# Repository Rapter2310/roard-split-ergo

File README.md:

# Roard Keyboard

Roard is a custom wireless split keyboard I designed, heavily based on the Lily58. The main physical difference is the layout. I modified it to include a dedicated arrow key cluster on the right half. 

The biggest technical difference is the wireless setup. Instead of standard Bluetooth, I'm using a 3-node Nordic Enhanced ShockBurst (ESB) configuration. The left and right halves connect to a third nice!nano plugged into the PC acting as a dedicated dongle, which fixes the latency and connection drops you sometimes get with standard BLE splits.

## Hardware Details
* **Controllers:** 3x nice!nano v2 (left, right, and central dongle).
* **Displays:** 2x nice!view screens.
* **Switches & Sockets:** Gateron Aliaz (silent tactiles) seated in Kailh MX hotswap sockets.
* **Power:** 3.7v 110mAh LiPo batteries.
* **Components & Assembly:** Sourced all the board-level SMD components (diodes, power/reset switches, battery connectors, and sockets) directly from Typeractive, and assembled the board using Kester solder wire.
* **Design Tools:** The core layout was built in Keyboard Layout Editor (KLE). I initially used the ai03 plate generator for rapid prototyping to test different angles and ergonomics before committing to the board design. To map the final physical matrix to the firmware, I used the [ZMK Physical Layout Converter](https://zmk-physical-layout-converter.streamlit.app/) to translate the KLE JSON directly into ZMK layout macros. The raw design files are in the `/design` folder.
* **PCB:** Custom routed in KiCad. Once the routing and standoff placements were finalized, I exported the board as a STEP file to serve as the foundation for the mechanical design.

## Case & Mechanical
I modeled the enclosure from scratch in Onshape. To guarantee perfect switch alignment and mounting hole clearance, I imported the KiCad STEP file directly into my Onshape workspace and traced the final switch plates and case standoffs around the exact geometry of the PCB.

I used a few different materials for the 3D printed parts depending on what they needed to do:
* **Case & Switch Plate:** PETG for general strength.
* **Tenting Kit:** TPU so it actually grips the desk and dampens the sound a bit.
* **Display Covers:** PLA to protect the nice!view screens.
Everything is held together with standard brass standoffs.

## Current Status & WIP
The board is fully functional as my daily driver, but I'm currently working on two main things:

1. **Customizing the nice!view Screens:** Switching from standard BLE to the ESB dongle setup breaks the standard `nice!view` widget implementation, which relies on BLE Zephyr services to report full connection states. Currently, the screens are running a basic fallback ZMK display profile that only outputs battery levels. I am actively rewriting the display logic to pull layer information and connection states over the ESB protocol to restore full functionality.
2. **Custom Keycaps:** I'm in the process of generating and 3D printing a custom keycap profile using [PseudoMakeMeKeyCapProfiles](https://github.com/pseudoku/PseudoMakeMeKeyCapProfiles).

## Repository Structure
* `/design`: KLE json files and prototyping assets.
* `/docs`: Photos of the finished board, the PCB, and the tenting kit.
* `/firmware`: ZMK config files, custom shield definitions, and ESB dongle setup.
* `/hardware`: KiCad project files, schematics, and production-ready Gerbers.
* `/mechanical`: STLs for 3D printing and STEP files exported from Onshape.

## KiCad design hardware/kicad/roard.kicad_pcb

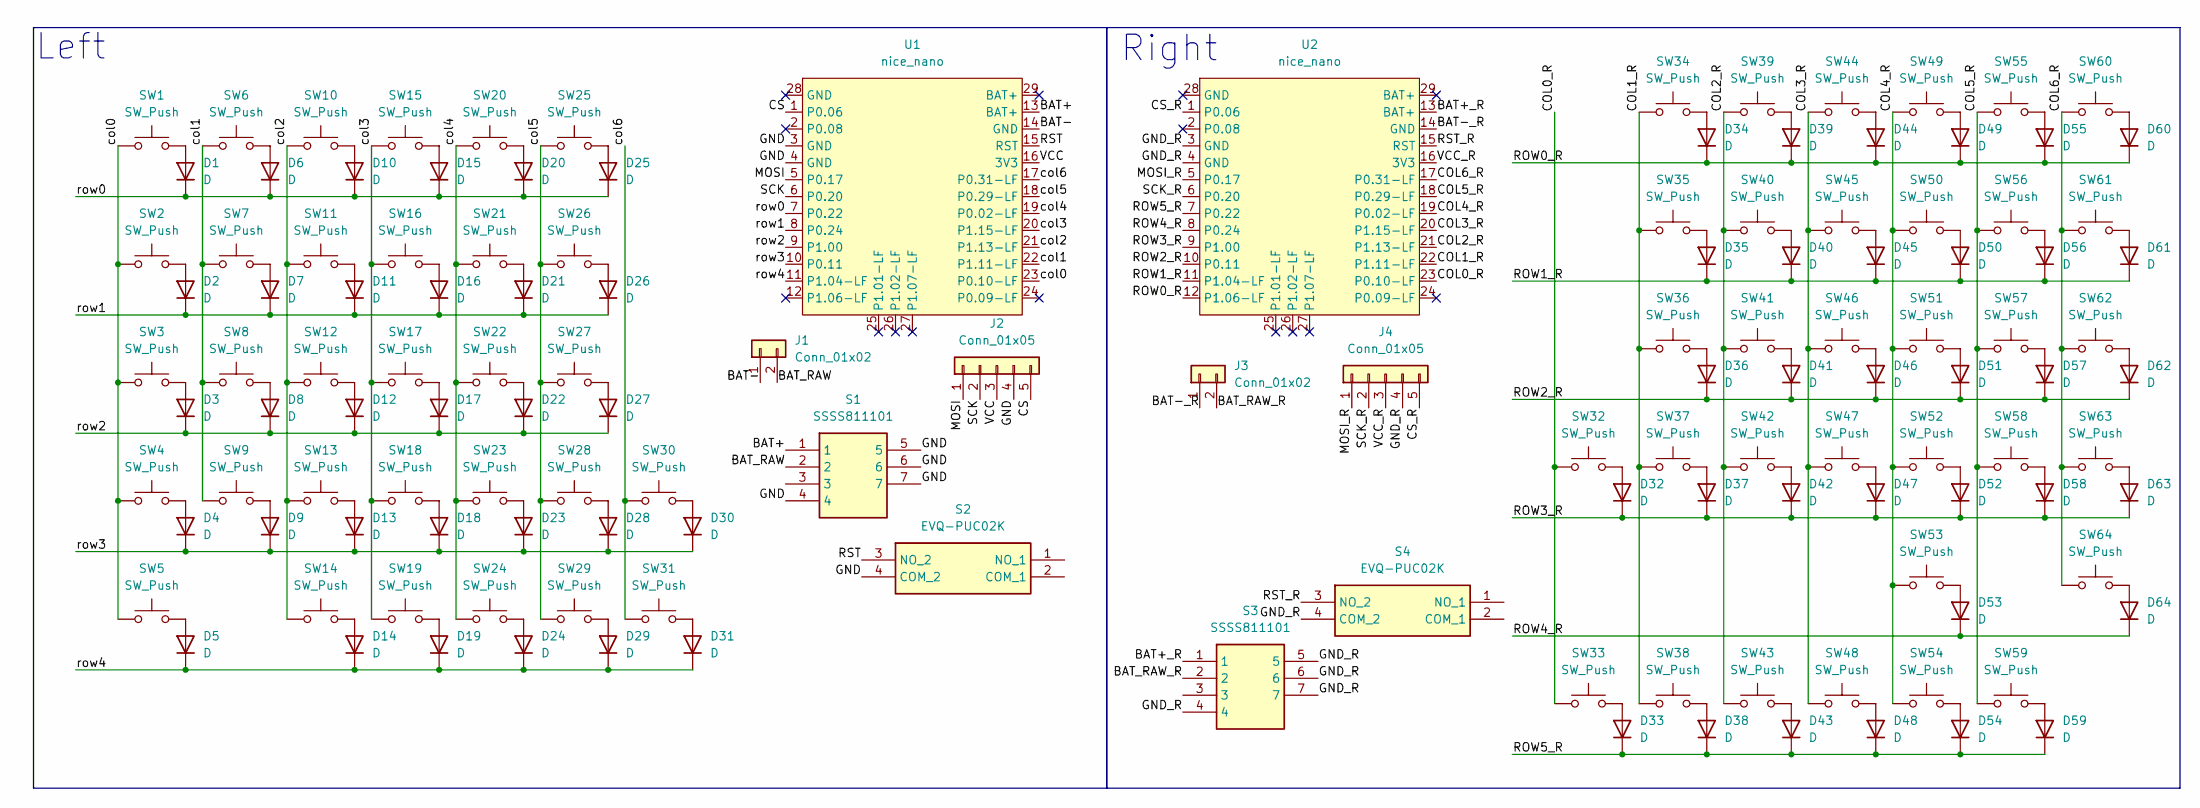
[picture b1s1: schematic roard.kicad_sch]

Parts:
D1, D2, D3, D4, D5, D6, D7, D8, D9, D10, D11, D12, D13, D14, D15, D16, D17, D18, D19, D20, D21, D22, D23, D24, D25, D26, D27, D28, D29, D30, D31, D32, D33, D34, D35, D36, D37, D38, D39, D40, D41, D42, D43, D44, D45, D46, D47, D48, D49, D50, D51, D52, D53, D54, D55, D56, D57, D58, D59, D60, D61, D62, D63, D64: D; D_SOD-123
J1, J3: Conn_01x02; JST_PH_S2B-PH-K_1x02_P2.00mm_Horizontal
J2, J4: Conn_01x05; PinHeader_1x05_P2.54mm_Vertical
S1, S3: SSSS811101; Mouser Part Number 688-SSSS811101
S2, S4: EVQ-PUC02K; EVQPUC02K; Mouser Part Number 667-EVQ-PUC02K
SW1, SW2, SW3, SW4, SW5, SW6, SW7, SW8, SW9, SW10, SW11, SW12, SW13, SW14, SW15, SW16, SW17, SW18, SW19, SW20, SW21, SW22, SW23, SW24, SW25, SW26, SW27, SW28, SW29, SW30, SW31, SW32, SW33, SW34, SW35, SW36, SW37, SW38, SW39, SW40, SW41, SW42, SW43, SW44, SW45, SW46, SW47, SW48, SW49, SW50, SW51, SW52, SW53, SW54, SW55, SW56, SW57, SW58, SW59, SW60, SW61, SW62, SW63, SW64: SW_Push; SW_Hotswap_Kailh_MX
U1, U2: nice_nano; nice_nano_pinChange

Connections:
/BAT+: S1.1, U1.13 (BAT+)
/BAT+_R: S3.1, U2.13 (BAT+)
/BAT-: J1.1, U1.14 (GND)
/BAT-_R: J3.1, U2.14 (GND)
/BAT_RAW: J1.2, S1.2
/BAT_RAW_R: J3.2, S3.2
/COL0_R: SW32.1, SW33.1, U2.23 (P0.10-LF)
/COL1_R: SW34.1, SW35.1, SW36.1, SW37.1, SW38.1, U2.22 (P1.11-LF)
/COL2_R: SW39.1, SW40.1, SW41.1, SW42.1, SW43.1, U2.21 (P1.13-LF)
/COL3_R: SW44.1, SW45.1, SW46.1, SW47.1, SW48.1, U2.20 (P1.15-LF)
/COL4_R: SW49.1, SW50.1, SW51.1, SW52.1, SW53.1, SW54.1, U2.19 (P0.02-LF)
/COL5_R: SW55.1, SW56.1, SW57.1, SW58.1, SW59.1, U2.18 (P0.29-LF)
/COL6_R: SW60.1, SW61.1, SW62.1, SW63.1, SW64.1, U2.17 (P0.31-LF)
/CS: J2.5, U1.1 (P0.06)
/CS_R: J4.5, U2.1 (P0.06)
/GND: J2.4, S1.4, S1.5, S1.6, S1.7, S2.4 (COM_2), U1.3 (GND), U1.4 (GND)
/GND_R: J4.4, S3.4, S3.5, S3.6, S3.7, S4.4 (COM_2), U2.3 (GND), U2.4 (GND)
/MOSI: J2.1, U1.5 (P0.17)
/MOSI_R: J4.1, U2.5 (P0.17)
/ROW0_R: D34.1 (K), D39.1 (K), D44.1 (K), D49.1 (K), D55.1 (K), D60.1 (K), U2.12 (P1.06-LF)
/ROW1_R: D35.1 (K), D40.1 (K), D45.1 (K), D50.1 (K), D56.1 (K), D61.1 (K), U2.11 (P1.04-LF)
/ROW2_R: D36.1 (K), D41.1 (K), D46.1 (K), D51.1 (K), D57.1 (K), D62.1 (K), U2.10 (P0.11)
/ROW3_R: D32.1 (K), D37.1 (K), D42.1 (K), D47.1 (K), D52.1 (K), D58.1 (K), D63.1 (K), U2.9 (P1.00)
/ROW4_R: D53.1 (K), D64.1 (K), U2.8 (P0.24)
/ROW5_R: D33.1 (K), D38.1 (K), D43.1 (K), D48.1 (K), D54.1 (K), D59.1 (K), U2.7 (P0.22)
/RST: S2.3 (NO_2), U1.15 (RST)
/RST_R: S4.3 (NO_2), U2.15 (RST)
/SCK: J2.2, U1.6 (P0.20)
/SCK_R: J4.2, U2.6 (P0.20)
/VCC: J2.3, U1.16 (3V3)
/VCC_R: J4.3, U2.16 (3V3)
/col0: SW1.1, SW2.1, SW3.1, SW4.1, SW5.1, U1.23 (P0.10-LF)
/col1: SW6.1, SW7.1, SW8.1, SW9.1, U1.22 (P1.11-LF)
/col2: SW10.1, SW11.1, SW12.1, SW13.1, SW14.1, U1.21 (P1.13-LF)
/col3: SW15.1, SW16.1, SW17.1, SW18.1, SW19.1, U1.20 (P1.15-LF)
/col4: SW20.1, SW21.1, SW22.1, SW23.1, SW24.1, U1.19 (P0.02-LF)
/col5: SW25.1, SW26.1, SW27.1, SW28.1, SW29.1, U1.18 (P0.29-LF)
/col6: SW30.1, SW31.1, U1.17 (P0.31-LF)
/row0: D1.1 (K), D6.1 (K), D10.1 (K), D15.1 (K), D20.1 (K), D25.1 (K), U1.7 (P0.22)
/row1: D2.1 (K), D7.1 (K), D11.1 (K), D16.1 (K), D21.1 (K), D26.1 (K), U1.8 (P0.24)
/row2: D3.1 (K), D8.1 (K), D12.1 (K), D17.1 (K), D22.1 (K), D27.1 (K), U1.9 (P1.00)
/row3: D4.1 (K), D9.1 (K), D13.1 (K), D18.1 (K), D23.1 (K), D28.1 (K), D30.1 (K), U1.10 (P0.11)
/row4: D5.1 (K), D14.1 (K), D19.1 (K), D24.1 (K), D29.1 (K), D31.1 (K), U1.11 (P1.04-LF)
unnamed: D1.2 (A), SW1.2
unnamed: D2.2 (A), SW2.2
unnamed: D3.2 (A), SW3.2
unnamed: D4.2 (A), SW4.2
unnamed: D5.2 (A), SW5.2
unnamed: D6.2 (A), SW6.2
unnamed: D7.2 (A), SW7.2
unnamed: D8.2 (A), SW8.2
unnamed: D9.2 (A), SW9.2
unnamed: D10.2 (A), SW10.2
unnamed: D11.2 (A), SW11.2
unnamed: D12.2 (A), SW12.2
unnamed: D13.2 (A), SW13.2
unnamed: D14.2 (A), SW14.2
unnamed: D15.2 (A), SW15.2
unnamed: D16.2 (A), SW16.2
unnamed: D17.2 (A), SW17.2
unnamed: D18.2 (A), SW18.2
unnamed: D19.2 (A), SW19.2
unnamed: D20.2 (A), SW20.2
unnamed: D21.2 (A), SW21.2
unnamed: D22.2 (A), SW22.2
unnamed: D23.2 (A), SW23.2
unnamed: D24.2 (A), SW24.2
unnamed: D25.2 (A), SW25.2
unnamed: D26.2 (A), SW26.2
unnamed: D27.2 (A), SW27.2
unnamed: D28.2 (A), SW28.2
unnamed: D29.2 (A), SW29.2
unnamed: D30.2 (A), SW30.2
unnamed: D31.2 (A), SW31.2
unnamed: D32.2 (A), SW32.2
unnamed: D33.2 (A), SW33.2
unnamed: D34.2 (A), SW34.2
unnamed: D35.2 (A), SW35.2
unnamed: D36.2 (A), SW36.2
unnamed: D37.2 (A), SW37.2
unnamed: D38.2 (A), SW38.2
unnamed: D39.2 (A), SW39.2
unnamed: D40.2 (A), SW40.2
unnamed: D41.2 (A), SW41.2
unnamed: D42.2 (A), SW42.2
unnamed: D43.2 (A), SW43.2
unnamed: D44.2 (A), SW44.2
unnamed: D45.2 (A), SW45.2
unnamed: D46.2 (A), SW46.2
unnamed: D47.2 (A), SW47.2
unnamed: D48.2 (A), SW48.2
unnamed: D49.2 (A), SW49.2
unnamed: D50.2 (A), SW50.2
unnamed: D51.2 (A), SW51.2
unnamed: D52.2 (A), SW52.2
unnamed: D53.2 (A), SW53.2
unnamed: D54.2 (A), SW54.2
unnamed: D55.2 (A), SW55.2
unnamed: D56.2 (A), SW56.2
unnamed: D57.2 (A), SW57.2
unnamed: D58.2 (A), SW58.2
unnamed: D59.2 (A), SW59.2
unnamed: D60.2 (A), SW60.2
unnamed: D61.2 (A), SW61.2
unnamed: D62.2 (A), SW62.2
unnamed: D63.2 (A), SW63.2
unnamed: D64.2 (A), SW64.2

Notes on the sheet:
Right
Left

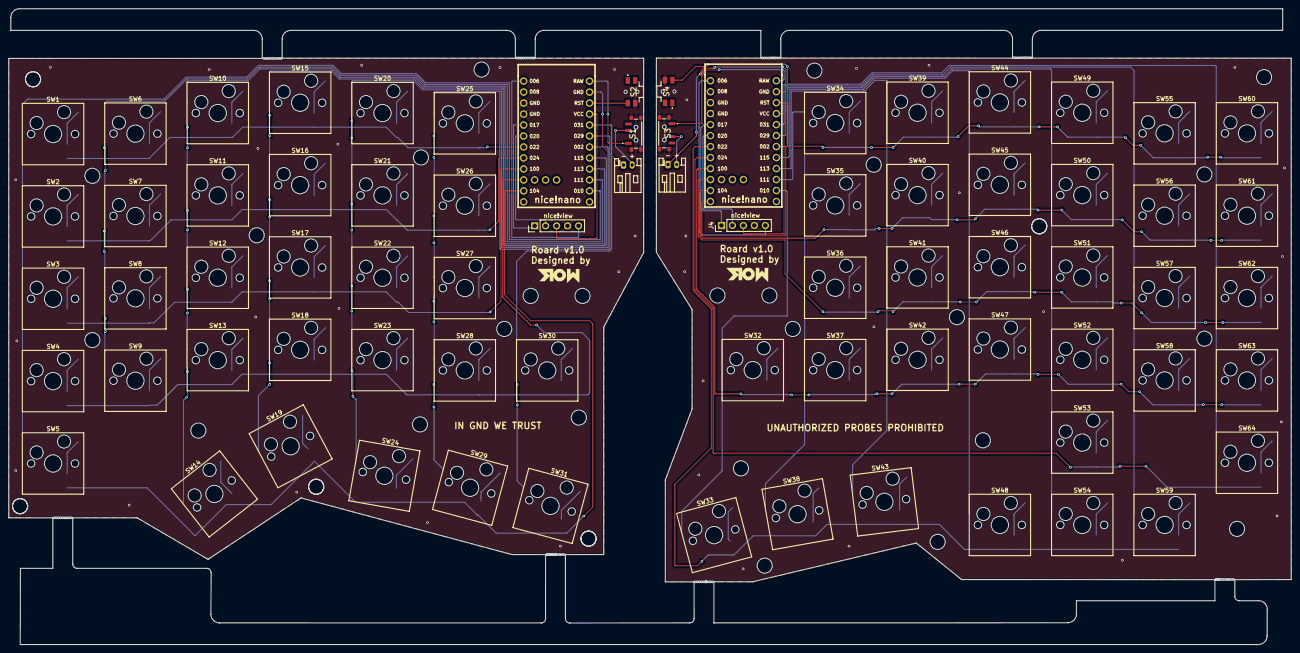
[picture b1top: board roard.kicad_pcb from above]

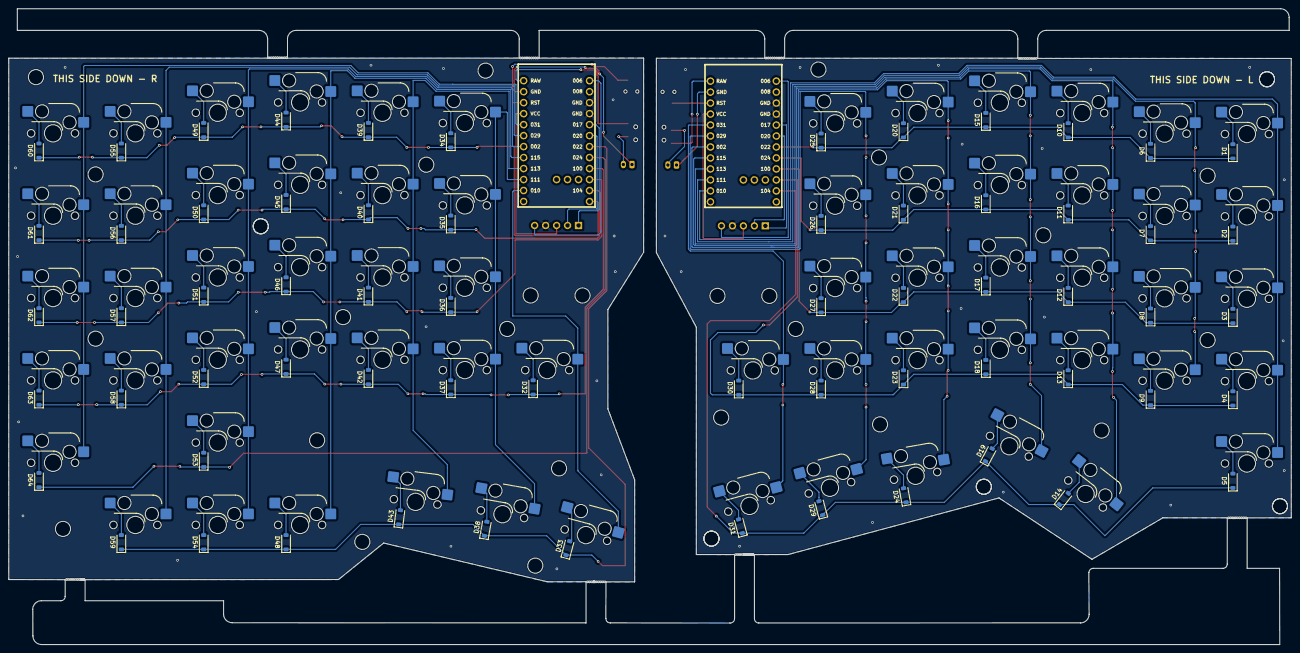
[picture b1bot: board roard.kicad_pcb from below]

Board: 2 copper layers, 296.7 x 147.1 mm, 140 parts (64 on the bottom side), 107 nets.

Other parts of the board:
H4, H15: tab; breakaway04

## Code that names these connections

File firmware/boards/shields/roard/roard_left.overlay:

#include "roard.dtsi"

&kscan {
    row-gpios =
          <&gpio0 22 (GPIO_ACTIVE_HIGH | GPIO_PULL_DOWN)>  /* row0: P0.22 */
        , <&gpio0 24 (GPIO_ACTIVE_HIGH | GPIO_PULL_DOWN)>  /* row1: P0.24 */
        , <&gpio1 0  (GPIO_ACTIVE_HIGH | GPIO_PULL_DOWN)>  /* row2: P1.00 */
        , <&gpio0 11 (GPIO_ACTIVE_HIGH | GPIO_PULL_DOWN)>  /* row3: P0.11 */
        , <&gpio1 4  (GPIO_ACTIVE_HIGH | GPIO_PULL_DOWN)>  /* row4: P1.04 */
        ;

    col-gpios =
          <&gpio0 10 GPIO_ACTIVE_HIGH> /* col0: P0.10 */
        , <&gpio1 11 GPIO_ACTIVE_HIGH> /* col1: P1.11 */
        , <&gpio1 13 GPIO_ACTIVE_HIGH> /* col2: P1.13 */
        , <&gpio1 15 GPIO_ACTIVE_HIGH> /* col3: P1.15 */
        , <&gpio0 2  GPIO_ACTIVE_HIGH> /* col4: P0.02 */
        , <&gpio0 29 GPIO_ACTIVE_HIGH> /* col5: P0.29 */
        , <&gpio0 31 GPIO_ACTIVE_HIGH> /* col6: P0.31 */
        ;
};

/ {
    esb_split {
        compatible = "zmk,esb-split";
        base-addr-0 = <0xE7 0xF1 0xB3 0x4C>;
        base-addr-1 = <0xC2 0x3D 0xA7 0x7B>;
        addr-prefix = <0xE7 0xC2 0x3C 0xC4 0x5D 0xA9 0xF5 0xC8>;
    };
};

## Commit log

2026-04-15 MIT License
